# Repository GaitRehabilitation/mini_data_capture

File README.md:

# Mini Data Capture

## Programming

```avrdude -c <programmer> -p atmega328 -b 57600  -U flash:w:main.hex -U lfuse:w:0xff:m -U hfuse:w:0xd1:m -U efuse:w:0xff:m```

[Fuse Calculator](http://eleccelerator.com/fusecalc/fusecalc.php?chip=atmega328p)

## Maintainers

The current maintainers of this repository are:

* Michael Pollind <polli104@mail.chapman.edu>

# License

```
/**
* Copyright 2018 GaitRehabilitation
*
* Licensed under the Apache License, Version 2.0 (the "License");
* you may not use this file except in compliance with the License.
* You may obtain a copy of the License at
*
*     http://www.apache.org/licenses/LICENSE-2.0
*
* Unless required by applicable law or agreed to in writing, software
* distributed under the License is distributed on an "AS IS" BASIS,
* WITHOUT WARRANTIES OR CONDITIONS OF ANY KIND, either express or implied.
* See the License for the specific language governing permissions and
* limitations under the License.
*/

```

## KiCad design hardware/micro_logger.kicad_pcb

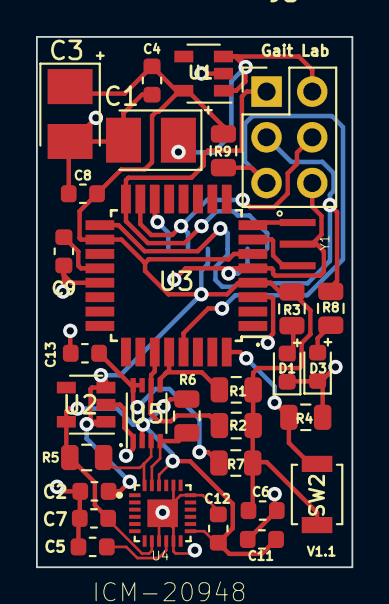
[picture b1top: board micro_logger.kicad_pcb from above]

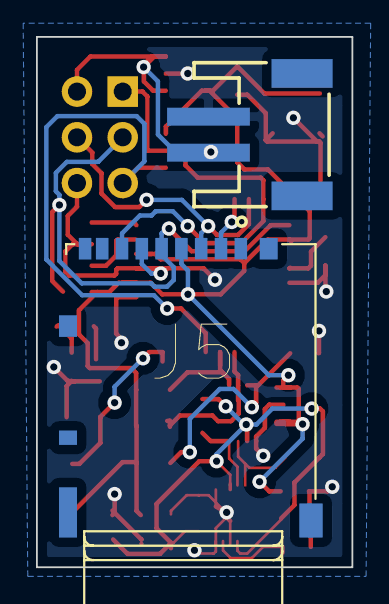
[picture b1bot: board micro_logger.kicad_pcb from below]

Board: 2 copper layers, 17.5 x 29.5 mm, 33 parts (2 on the bottom side), 21 nets.

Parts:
C1: 10uF; CP_Tantalum_Case-T_EIA-3528-12_Reflow
C2, C7: 1uF; C_0603_1608Metric
C3: 10uF; CP_Tantalum_Case-B_EIA-3528-21_Reflow
C4, C5, C6, C11, C12: .1uF; C_0603_1608Metric
C8, C9: .1uf; C_0603_1608Metric
C13: 100pF; C_0603_1608Metric
D1: LED; LED_0603_1608Metric
D3: LD271; LED_0603_1608Metric
J3: ISP; PinHeader_2x03_P2.54mm_Vertical
J4: Conn_01x02; JSTPH2
J5: DM3AT-SF-PEJM5; HRS_DM3AT-SF-PEJM5
R1, R2, R5, R6: 10K; R_0805_2012Metric
R3, R4, R9: 10k; R_0805_2012Metric
R7: 200K; R_0805_2012Metric
R8: 330; R_0805_2012Metric
SW2: SW_Push; SW_SPST_B3U-1000P
U1: MIC5205-3.3; SOT-23-5
U2: TLV70218_SOT23-5; SOT-23-5
U3: ATMEGA328-AU; TQFP-32_7x7mm_P0.8mm
U4: ICM-20948
U5: PCA9306; VSSOP-8_2.3x2mm_P0.5mm
Y1: Crystal_GND2; OSC_CSTCE8M00G55-R0

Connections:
+1V8: C7.1, C11.2, C12.2, R5.1, R6.1, U2.5, U4.8, U4.13, U4.22, U5.2
+3V3: C2.1, C3.1, C4.1, C6.1, C8.1, J5.4, R1.1, R2.1, R3.2, R7.2, R9.1, SW2.2, U1.5, U2.1, U2.3, U3.4, U3.6, U3.18
/Ardunio/D2: R4.2, SW2.1, U3.32
/Ardunio/RESET: J3.5, R9.2, U3.29
CS: J5.2, U3.14
GND: C1.2, C2.2, C3.2, C4.2, C5.1, C6.2, C7.2, C8.2, C9.2, C11.1, C12.1, C13.2, D1.1, D3.1, J3.6, J4.1, J5.6, R4.1, U1.2, U2.2, U3.3, U3.5, U3.21, U4.9, U4.11, U4.18, U4.20, U4.25, U5.1, Y1.2
MISO: J3.1, J5.7, U3.16
MOSI: J3.4, J5.3, U3.15
unnamed: C5.2, U4.10
unnamed: C9.1, U3.20
unnamed: C13.1, R7.1, U5.7, U5.8
unnamed: D1.2, R3.1
unnamed: D3.2, R8.1
unnamed: R5.2, U4.24, U5.3
unnamed: R6.2, U4.23, U5.4
unnamed: U3.7, Y1.3
unnamed: U3.8, Y1.1
SCK: J3.3, J5.5, R8.2, U3.17
SCL_MPU: R1.2, U3.28, U5.5
SDA_MPU: R2.2, U3.27, U5.6
VCC: C1.1, J3.2, J4.2, U1.1, U1.3

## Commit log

2018-09-30 start
2018-09-30 adjusted layout
2018-09-30 cleaned up layout
2018-09-30 added gait logo
2018-09-30 updated border
2018-10-01 updated layout
2018-10-01 hid elements
2018-10-19 updated shift logic
2018-10-24 re-organized file structure
2018-10-24 removed old readme
2018-10-31 merged in firmware
2018-11-01 fixed registers
2018-11-02 fixed logging
2018-11-06 added bom
2018-11-06 updated symbols
2018-11-07 tweaked design for write performance
2018-11-17 updated schematic
2018-11-17 removed output.zip
2018-11-17 removed unused sheet
2018-11-19 removed overrun condition
2019-01-11 added preview and updated 3rdpart dependenices
2019-01-11 added decoder for seralized data file
2019-01-12 added a retry step
2019-01-12 fixed overwrite file condition
2019-01-22 added decoding app
2019-03-08 added appveyor build
2019-03-08 added repisotry section to deploy
2019-03-08 removed submodule
2019-03-08 fixed target
2019-03-08 set back to 4g and 1000deg/s along with decoding app
2019-03-08 moved thread implementation
2019-03-08 added to post event
2019-03-08 added queued connection
2019-03-11 fixed threading issue
2019-04-05 updated documentation
2019-04-06 added fuse configurations
2019-04-06 added link to fuse calculator
